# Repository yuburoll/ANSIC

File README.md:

[한국어 설명은 여기에서 보실 수 있습니다](README_ko.md)

# ANSIC

uniform row staggered 40~42 key split keyboard under 100x100mm PCB

The name "ansic" is repose in Korean.

## Preparation

- 2x pro micro (Approx. 4-8$)

- 2x ansic PCB Boards (5 boards are 2$ on JLC w/o shipping cost)

- 1x printed case sets, 2 parts total (Approx. 6$ if you buy printed one on JLC. Use braced ones or 2mm ones for 3d print)

- 2x keyboard plates (Approx. 4~12$ which method you use: 3DP, FR4 fab, CNC, laser cut. etc...)

- 2x back plates (Approx. 6~18$ which method you use: 3DP, FR4 fab, CNC, laser cut. etc..)

- 42x diodes (Approx. 1$)

- 20x M2x6 screws, flathead (Approx. 1$)

- 2x PJ320A 1/8(3.5mm) TRRS connector (Approx. 1$)

- 2x 4x4x1.5mm surface mount tact switches (Approx. 1$)

- 1x 1/8(3.5mm) TRRS cable (Approx. 2$, may TRS cable can take the place.)

- 44x MX Hotswap Sockets (Approx. 5$) (or, use soldering version)

- 0~2x Plate Mounted 2u Keyboard Stabilizers (Approx. 1$ when cheap)

- 40~42x MX Keyswitches & Keycaps (Maybe this cost varies too much. 15$ on average)

Approx. 49-73$(w/o shipping cost) needed to build one.

for wireless build, you may additionally need:

- 2x "Wireless" promicro (eg. nrf52840)

- 2x 12c02 slide switch (very fragile, so handle with caution)

- 2x printed power switch part

- 2x xx2030 Li-po battery (eg. 902030) and socket(in 1.25)

## Default Keymap

Holding the key triggers front legend.

There are two more layers - Symbol, Fn - which can be noticed by the color legends. ◇ Means Transparent; which uses base keymap.

## Build Guides

work in progress. sorry! I uploaded images for buildguide at [images](images) folder.

also you may refer to the pictures below:

#### Wired

**You may flash the firmware first before the build.** It's hard to make dfu mode after the build.

#### Wireless

## Note

On released version, they have merged thumb cluster based on SW21(outside thumb cluster).

(prototype) tagged versions are legacy file, which have merged thumb cluster based on SW20(middle thumb cluster). only the gerbers before Jan. 30, 2026 have those old schema.

Both Wired and Wireless version works well: proved by my two builds.

## Licenses

all codes follow MIT license.

all designs and the hardware board follow CC BY-SA 4.0 license.

If you want to make a commercial product, it would be appreciated if you sponsor some bucks for me.

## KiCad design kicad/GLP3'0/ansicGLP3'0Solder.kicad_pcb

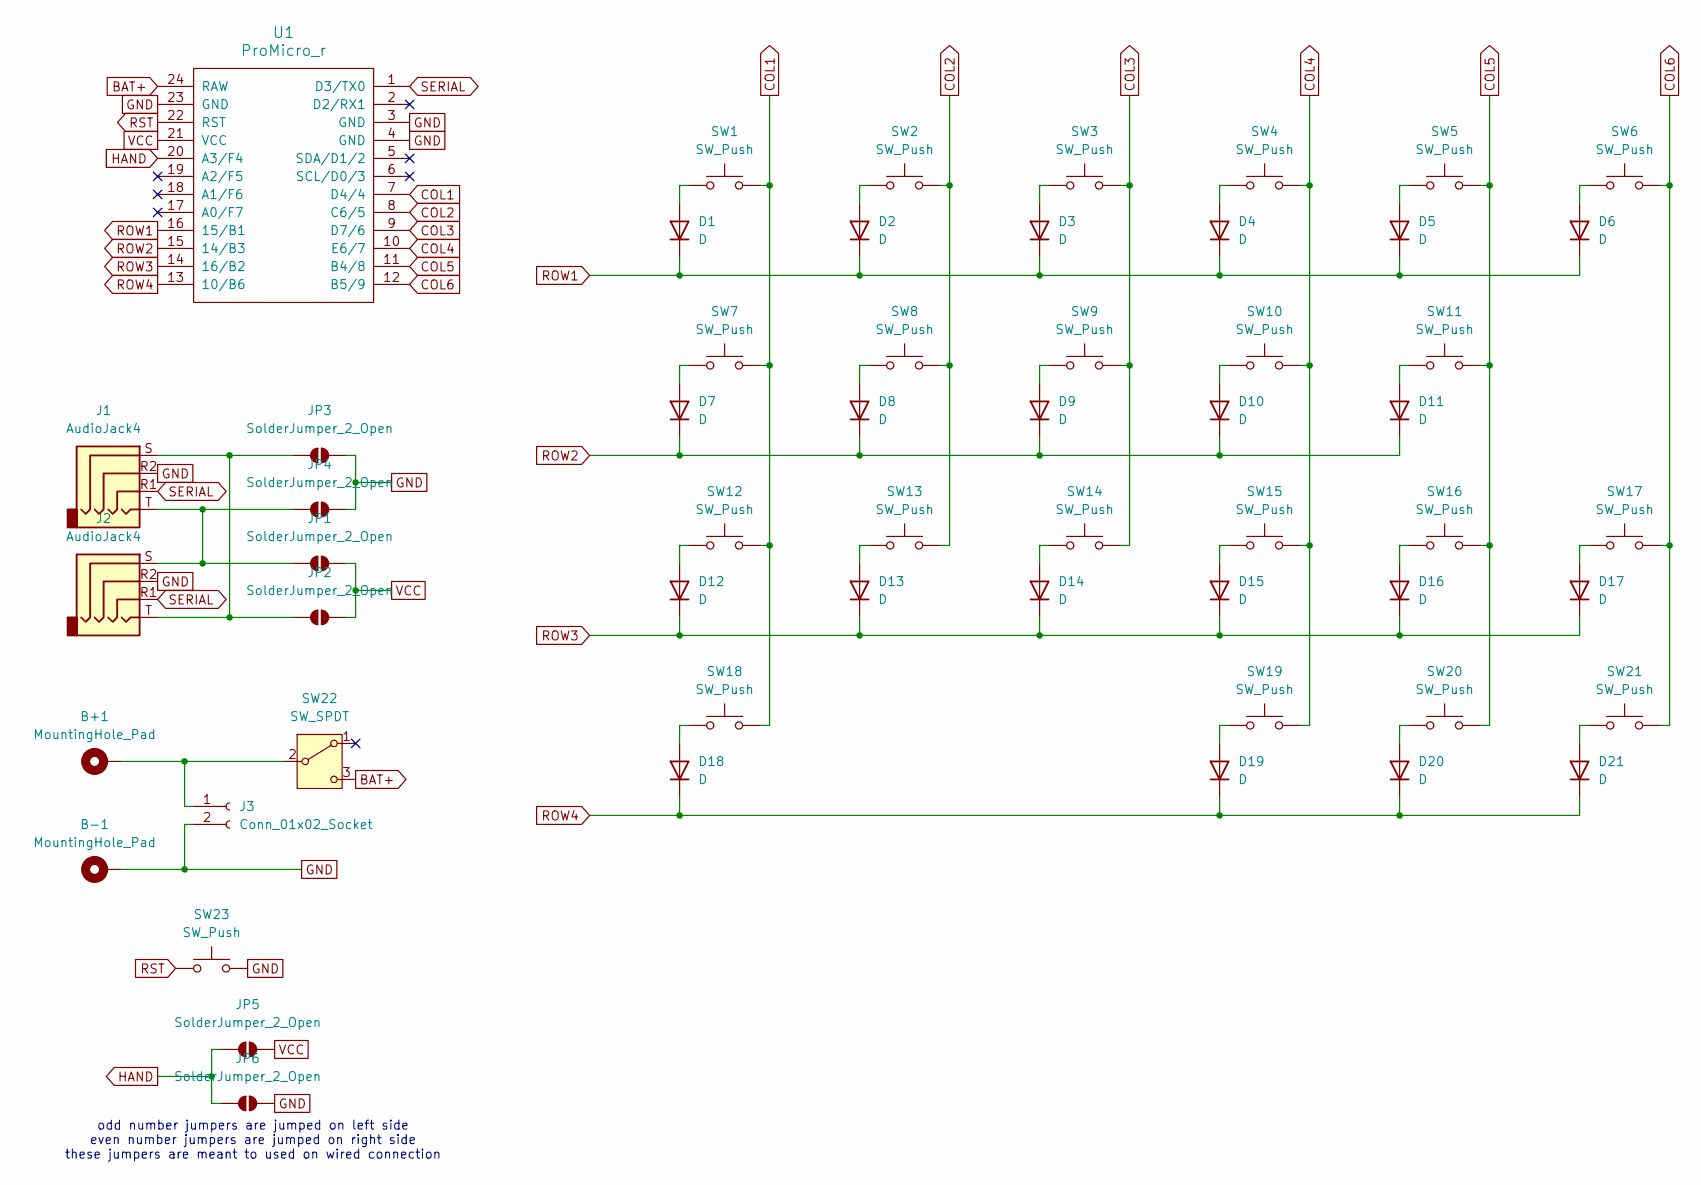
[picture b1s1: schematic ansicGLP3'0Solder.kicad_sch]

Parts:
B+1: MountingHole_Pad
B-1: MountingHole_Pad
D1, D2, D3, D4, D5, D6, D7, D8, D9, D10, D11, D12, D13, D14, D15, D16, D17, D18, D19, D20, D21: D
J1, J2: AudioJack4
J3: Conn_01x02_Socket
JP1, JP2, JP3, JP4, JP5, JP6: SolderJumper_2_Open
SW1, SW2, SW3, SW4, SW5, SW6, SW7, SW8, SW9, SW10, SW11, SW12, SW13, SW14, SW15, SW16, SW17, SW18, SW19, SW20, SW21, SW23: SW_Push
SW22: SW_SPDT
U1: ProMicro_r

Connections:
BAT+: SW22.3 (C), U1.24 (RAW); also elsewhere on the board
COL1: SW1.2, SW7.2, SW12.2, SW18.2, U1.7 (D4/4)
COL2: SW2.2, SW8.2, SW13.2, U1.8 (C6/5)
COL3: SW3.2, SW9.2, SW14.2, U1.9 (D7/6)
COL4: SW4.2, SW10.2, SW15.2, SW19.2, U1.10 (E6/7)
COL5: SW5.2, SW11.2, SW16.2, SW20.2, U1.11 (B4/8)
COL6: SW6.2, SW17.2, SW21.2, U1.12 (B5/9); also elsewhere on the board
GND: B-1.1, J1.R2, J2.R2, J3.2, JP3.2 (B), JP4.2 (B), JP6.1 (A), SW22.SH, SW23.2, U1.3 (GND), U1.4 (GND), U1.23 (GND); also elsewhere on the board
unnamed: D1.2 (A), SW1.1
unnamed: D2.2 (A), SW2.1
unnamed: D3.2 (A), SW3.1
unnamed: D4.2 (A), SW4.1
unnamed: D5.2 (A), SW5.1
unnamed: D6.2 (A), SW6.1
unnamed: D7.2 (A), SW7.1
unnamed: D8.2 (A), SW8.1
unnamed: D9.2 (A), SW9.1
unnamed: D10.2 (A), SW10.1
unnamed: D11.2 (A), SW11.1
unnamed: D12.2 (A), SW12.1
unnamed: D13.2 (A), SW13.1
unnamed: D14.2 (A), SW14.1
unnamed: D15.2 (A), SW15.1
unnamed: D16.2 (A), SW16.1
unnamed: D17.2 (A), SW17.1
unnamed: D18.2 (A), SW18.1
unnamed: D19.2 (A), SW19.1
unnamed: D20.2 (A), SW20.1
unnamed 28: D21.2 (A), SW21.1; also elsewhere on the board
unnamed 29: B+1.1, J3.1, SW22.2 (B); also elsewhere on the board
unnamed: J1.T, J2.S, JP1.1 (A), JP4.1 (A)
unnamed: J1.S, J2.T, JP2.1 (A), JP3.1 (A)
unnamed: JP5.2 (B), JP6.2 (B), U1.20 (A3/F4)
ROW1: D1.1 (K), D2.1 (K), D3.1 (K), D4.1 (K), D5.1 (K), D6.1 (K), U1.16 (15/B1)
ROW2: D7.1 (K), D8.1 (K), D9.1 (K), D10.1 (K), D11.1 (K), U1.15 (14/B3)
ROW3: D12.1 (K), D13.1 (K), D14.1 (K), D15.1 (K), D16.1 (K), D17.1 (K), U1.14 (16/B2)
ROW4: D18.1 (K), D19.1 (K), D20.1 (K), D21.1 (K), U1.13 (10/B6)
RST: SW23.1, U1.22 (RST); also elsewhere on the board
SERIAL: J1.R1, J2.R1, U1.1 (D3/TX0)
VCC: JP1.2 (B), JP2.2 (B), JP5.1 (A), U1.21 (VCC)

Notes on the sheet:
odd number jumpers are jumped on left side even number jumpers are jumped on right side these jumpers are meant to used on wired connection

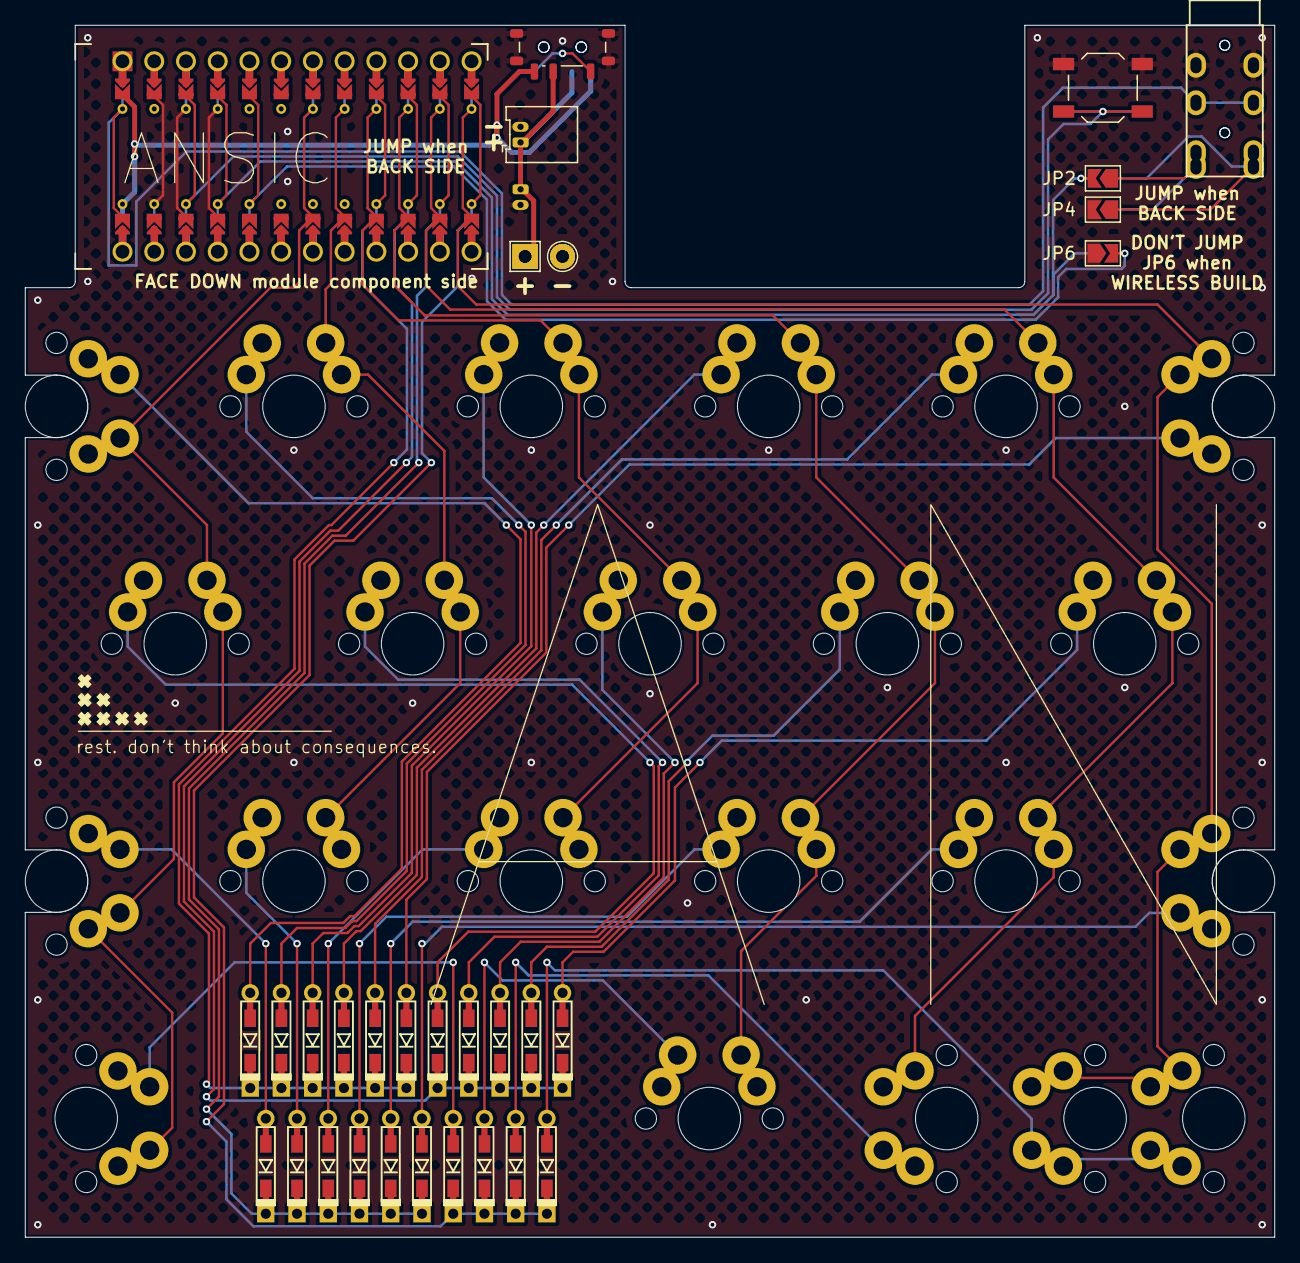
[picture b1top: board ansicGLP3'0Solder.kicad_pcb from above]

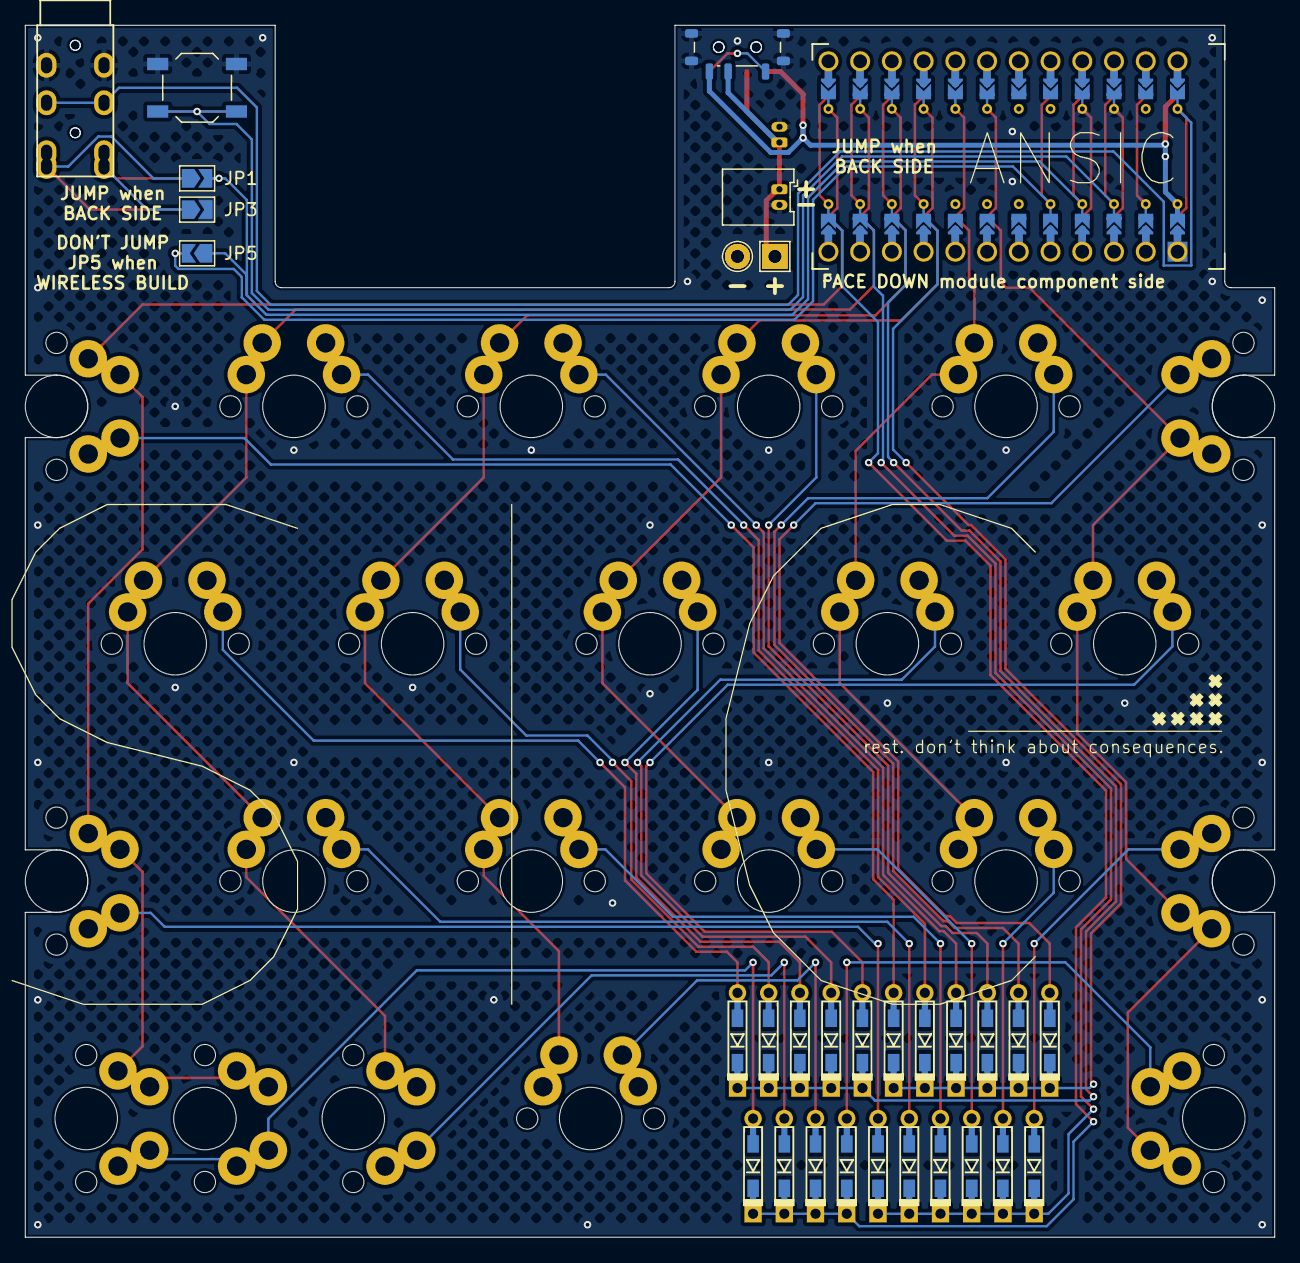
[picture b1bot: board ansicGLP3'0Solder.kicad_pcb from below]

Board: 2 copper layers, 100.0 x 97.0 mm, 62 parts (10 on the bottom side), 40 nets.

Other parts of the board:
B+1#2: MountingHole_Pad; TestPoint_THTPad_2.0x2.0mm_Drill1.0mm
B-1#2: MountingHole_Pad; TestPoint_THTPad_D2.0mm_Drill1.0mm
J3#2: Conn_01x02_Socket; Molex_PicoBlade_53048-0210_1x02_P1.25mm_Horizontal
SW21#2: SW_Push; MXGLP3'0_Mill-Max_FootprintPropertyFix
SW22#2: SW_SPDT; SW_SPDT_Shouhan_MSK12C02
SW23#2: SW_Push; SW_SPST_TL3342

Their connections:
BAT+: SW22#2.3 (C); also elsewhere on the board
COL6: SW21#2.2; also elsewhere on the board
GND: B-1#2.1, J3#2.2, SW22#2.SH, SW23#2.2; also elsewhere on the board
unnamed 28: SW21#2.1; also elsewhere on the board
unnamed 29: B+1#2.1, J3#2.1, SW22#2.2 (B); also elsewhere on the board
RST: SW23#2.1; also elsewhere on the board

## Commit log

2026-01-29 add license and readme
2026-01-29 add plates for fab
2026-01-29 change name ansik to ansic
2026-01-29 Rename aniscGerber.png to ansicGerber.png
2026-01-29 update case data
2026-01-30 move case hole to upper 0.5mm
2026-01-30 upload wired firmware
2026-01-30 edit readme
2026-01-30 add rp2040 qmk examples
2026-01-30 minor changes of firmware
2026-01-30 update keymap on example firmware
2026-01-30 move merge thumb layout matrix
2026-01-30 add solder version
2026-01-30 change gerber image
2026-01-31 fix confusing legend of silkscreen
2026-01-31 made bumpon place on backplate
2026-02-01 add mouse keymap
2026-02-03 edited case chamfer for more soft texture
2026-02-03 add switch to wireless case and tweak thumb chamfer
2026-02-03 add tweaked keymap and made prototype vial only
2026-02-03 add water drain backplate
2026-02-04 add bumpon and drain footprint
2026-02-04 edit for more readable schema
2026-02-04 change header image to new model
2026-02-07 fixed switch design for swapping
2026-02-07 add rmk wireless firmware
2026-02-07 thicken shield connectors to .6mm
2026-02-07 improve switch model
2026-02-07 image upload for build guide
2026-02-10 update keymap to compressed and theme controlled one
2026-02-10 name change for uniformed tag
2026-02-10 add korean readme
2026-02-11 kicad file for gateron lp 3.0
2026-02-12 update battery pin and name for rmk firmwares
2026-02-18 edit default keymap fn layer to more comfy one
2026-02-18 fix case inside error and make space for backplate
2026-02-18 add more thick version: 2mm
2026-02-18 bigger bridge for fdm and additional readme notice
